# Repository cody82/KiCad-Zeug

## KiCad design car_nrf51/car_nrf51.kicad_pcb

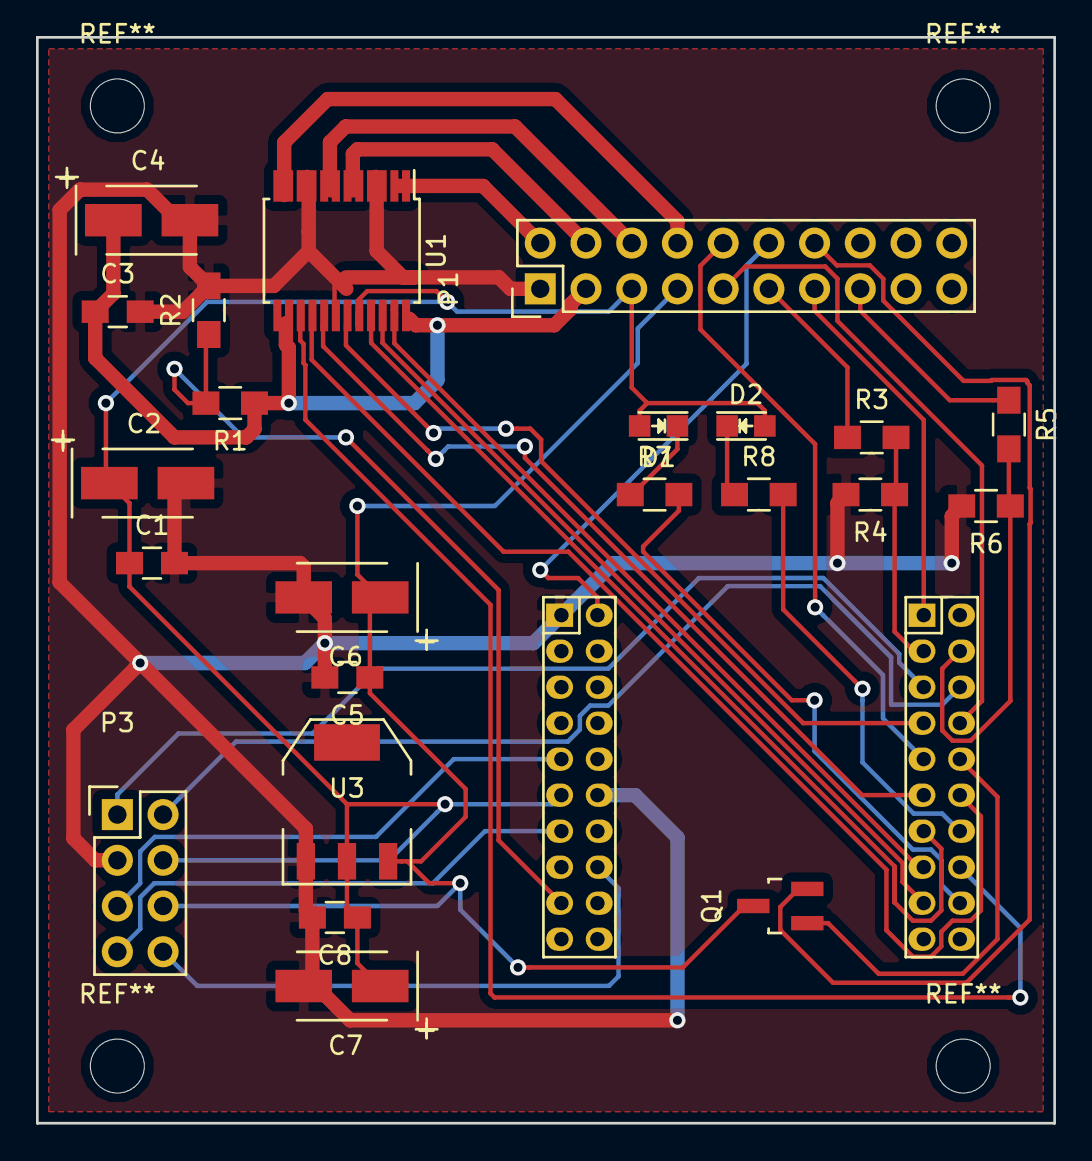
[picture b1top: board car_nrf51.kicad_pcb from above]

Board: 2 copper layers, 56.5 x 60.3 mm, 24 parts (0 on the bottom side), 35 nets.

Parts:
C1, C3: 100nF; C_0805_HandSoldering
C2, C4: 10uF; TantalC_SizeB_EIA-3528_HandSoldering
C5, C8: C; C_0805_HandSoldering
C6, C7: CP; TantalC_SizeB_EIA-3528_HandSoldering
D1, D2: LED; LED-0805
P1: CONN_02X10; Pin_Header_Straight_2x10
P2: nrf51-breakout
P3: CONN_02X04; Pin_Header_Straight_2x04
Q1: BC850; SOT-23_Handsoldering
R1, R2, R3, R4, R5, R6, R7, R8: R; R_0805_HandSoldering
U1: DRIVER-TB6612FNG-O/C8/EL(SSOP24); SSOP-24_5.3x8.2mm_Pitch0.65mm
U3: LM317_SOT223; SOT-223

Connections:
+3V3: C1.1, C2.1, C7.1, C8.1, D1.2, D2.2, P1.5, P2.11, P3.4, U1.20, U3.2
+5V: C5.1, C6.1, P1.7, P3.6, Q1.3, U3.3
/AIN1: P2.31, U1.21
/AIN2: P2.35, U1.22
/BIN1: P2.29, U1.17
/BIN2: P2.30, U1.16
/BackEcho3v: P2.22, R5.2, R6.1
/BackTrig: P1.13, P2.19
/BatVoltage: P2.17, R1.2, R2.1
/Beep: P1.14, Q1.2
/Beep3v3: P2.28, Q1.1
/FrontEcho3v: P2.21, R3.2, R4.1
/FrontTrig: P1.9, P2.26
/LED1: P2.36, R7.2
/LED2: P2.32, R8.2
/Light: P1.12, P2.2
/Motor1+: P1.2, U1.1, U1.2
/Motor1-: P1.4, U1.5, U1.6
/Motor2+: P1.6, U1.7, U1.8
/Motor2-: P1.8, U1.11, U1.12
/PWMA: P2.33, U1.23
/PWMB: P2.34, U1.15
/SCLK: P2.24, P3.2
/SDO: P2.23, P3.1
/STBY: P2.25, U1.19
/Servo: P1.10, P2.27
GND: C1.2, C2.2, C3.2, C4.2, C5.2, C6.2, C7.2, C8.2, P1.1, P2.1, P2.12, P3.3, R2.2, R4.2, R6.2, U1.3, U1.4, U1.9, U1.10, U1.18, U3.1
unnamed: D1.1, R7.1
unnamed: D2.1, R8.1
unnamed: P1.11, R3.1
unnamed: P1.15, R5.1
unnamed: P2.9, P3.5
unnamed: P2.13, P3.7
unnamed: P2.16, P3.8
VCC: C3.1, C4.1, P1.3, R1.1, U1.13, U1.14, U1.24

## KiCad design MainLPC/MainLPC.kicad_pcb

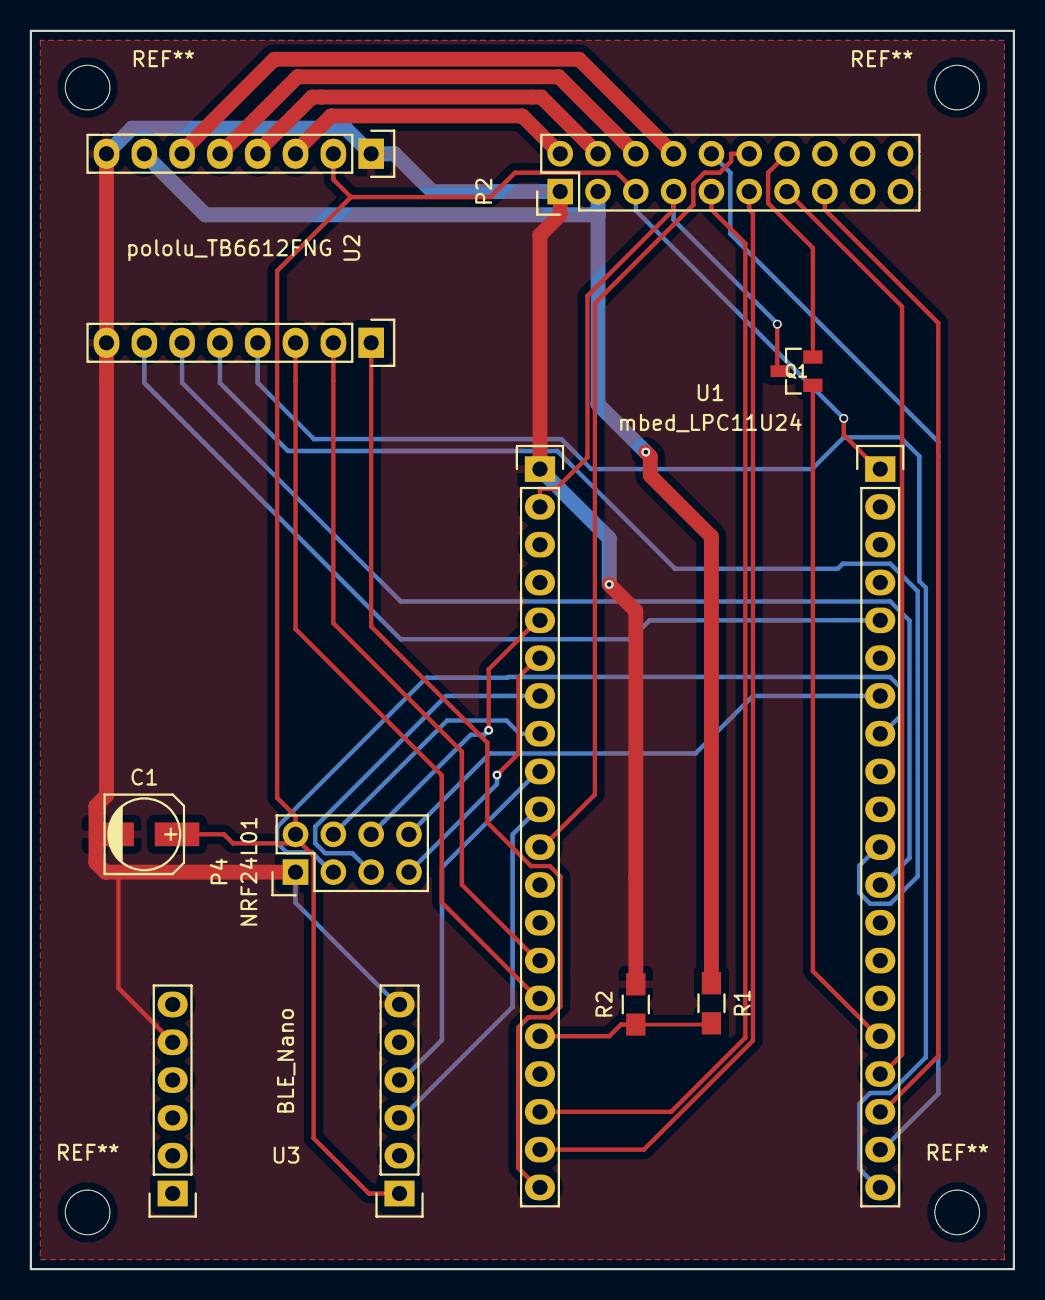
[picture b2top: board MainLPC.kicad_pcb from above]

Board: 2 copper layers, 66.0 x 83.2 mm, 9 parts (0 on the bottom side), 32 nets.

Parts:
C1: 20uF; c_elec_5x5.3
P2: CONN_02X10; Pin_Header_Straight_2x10
P4: NRF24L01; Pin_Header_Straight_2x04
Q1: BC850; SOT-23
R1, R2: R; R_0805_HandSoldering
U1: mbed_LPC11U24; mbed_LPC11U35
U2: pololu_TB6612FNG
U3: BLE_Nano; RedBearLab_BLE_Nano

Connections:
+3V3: C1.1, P2.5, P4.2, U1.40, U2.2, U3.1
+5V: P2.7, Q1.3, U1.2
/AIN1: U1.15, U2.11
/AIN2: U1.14, U2.10
/BIN1: U1.30, U2.13
/BIN2: U1.29, U2.14
/Beep: P2.14, Q1.2
/Light: P2.12, U1.11
/Motor1+: P2.2, U2.3
/Motor1-: P2.4, U2.4
/Motor2+: P2.6, U2.5
/Motor2-: P2.8, U2.6
/PwmA: U1.20, U2.9
/PwmB: U1.36, U2.15
/Servo: P2.10, U1.22
/Standby: U1.21, U2.12
/US_BackEcho: P2.15, U1.23
/US_BackTrig: P2.13, U1.24
/US_FrontEcho: P2.11, U1.19
/US_FrontTrig: P2.9, U1.18
GND: C1.2, P2.1, P4.1, R2.2, U1.1, U2.1, U2.8, U2.16, U3.6, U3.11
unnamed: P4.3, U1.33
unnamed: P4.4, U1.8
unnamed: P4.5, U1.7
unnamed: P4.6, U1.5
unnamed: P4.7, U1.6
unnamed: P4.8, U1.34
unnamed: Q1.1, U1.25
unnamed: R1.2, R2.1, U1.16
unnamed: U1.9, U3.4
unnamed: U1.10, U3.3
VCC: P2.3, R1.1, U2.7

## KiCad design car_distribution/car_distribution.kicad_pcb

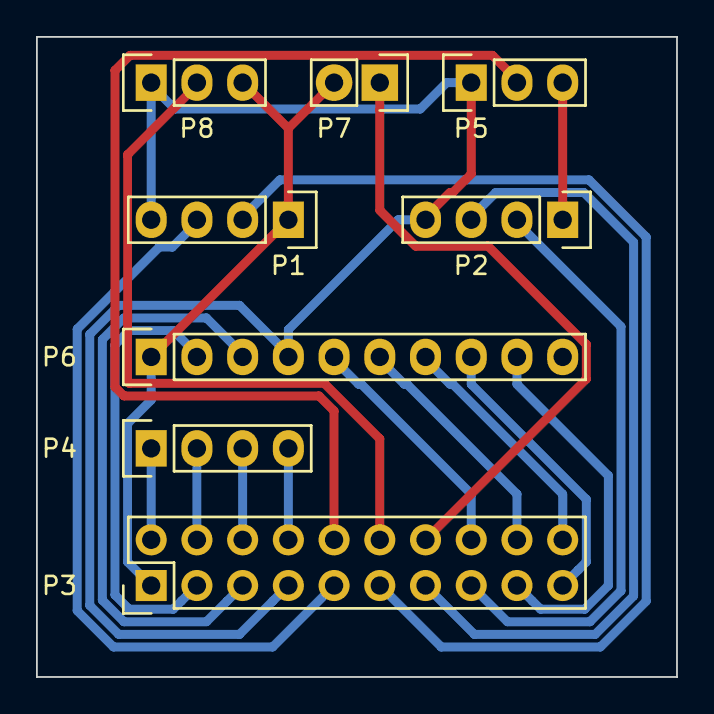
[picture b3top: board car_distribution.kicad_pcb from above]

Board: 2 copper layers, 35.6 x 35.6 mm, 8 parts (0 on the bottom side), 20 nets.

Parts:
P1: US_FRONT; Pin_Header_Straight_1x04
P2: US_BACK; Pin_Header_Straight_1x04
P3: CONN; Pin_Header_Straight_2x10
P4: MOTORS; Pin_Header_Straight_1x04
P5: SERVO; Pin_Header_Straight_1x03
P6: MISC; Pin_Header_Straight_1x10
P7: BEEP; Pin_Header_Straight_1x02
P8: LIGHT; Pin_Header_Straight_1x03

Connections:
+3V3: P3.5, P6.3
+5V: P1.4, P2.4, P3.7, P5.1, P6.4, P8.1
GND: P1.1, P2.1, P3.1, P5.3, P6.1, P7.2, P8.3
unnamed: P1.2, P3.11
unnamed: P1.3, P3.9
unnamed: P2.2, P3.15
unnamed: P2.3, P3.13
unnamed: P3.2, P4.1
unnamed: P3.4, P4.2
unnamed: P3.6, P4.3
unnamed: P3.8, P4.4
unnamed: P3.10, P5.2
unnamed: P3.12, P8.2
unnamed: P3.14, P7.1
unnamed: P3.16, P6.5
unnamed: P3.17, P6.9
unnamed: P3.18, P6.6
unnamed: P3.19, P6.8
unnamed: P3.20, P6.7
VCC: P3.3, P6.2

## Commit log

2015-09-19 Initial commit.
2015-12-20 Add new nrf51 board.
2015-12-20 Send to pcb service.
2016-01-23 Fix motor driver footprint.
2016-01-24 Increase via pad size to 0.9mm.
2016-01-26 Fix ground plane.
2016-02-14 Fix light connection.
2016-02-28 Add missing resistor and capacitor values.
2016-04-25 lipo sensor board
2016-06-16 Set resistor values.
2016-06-18 Update values.
2016-06-18 Move lipo_sensor to its own repo.
